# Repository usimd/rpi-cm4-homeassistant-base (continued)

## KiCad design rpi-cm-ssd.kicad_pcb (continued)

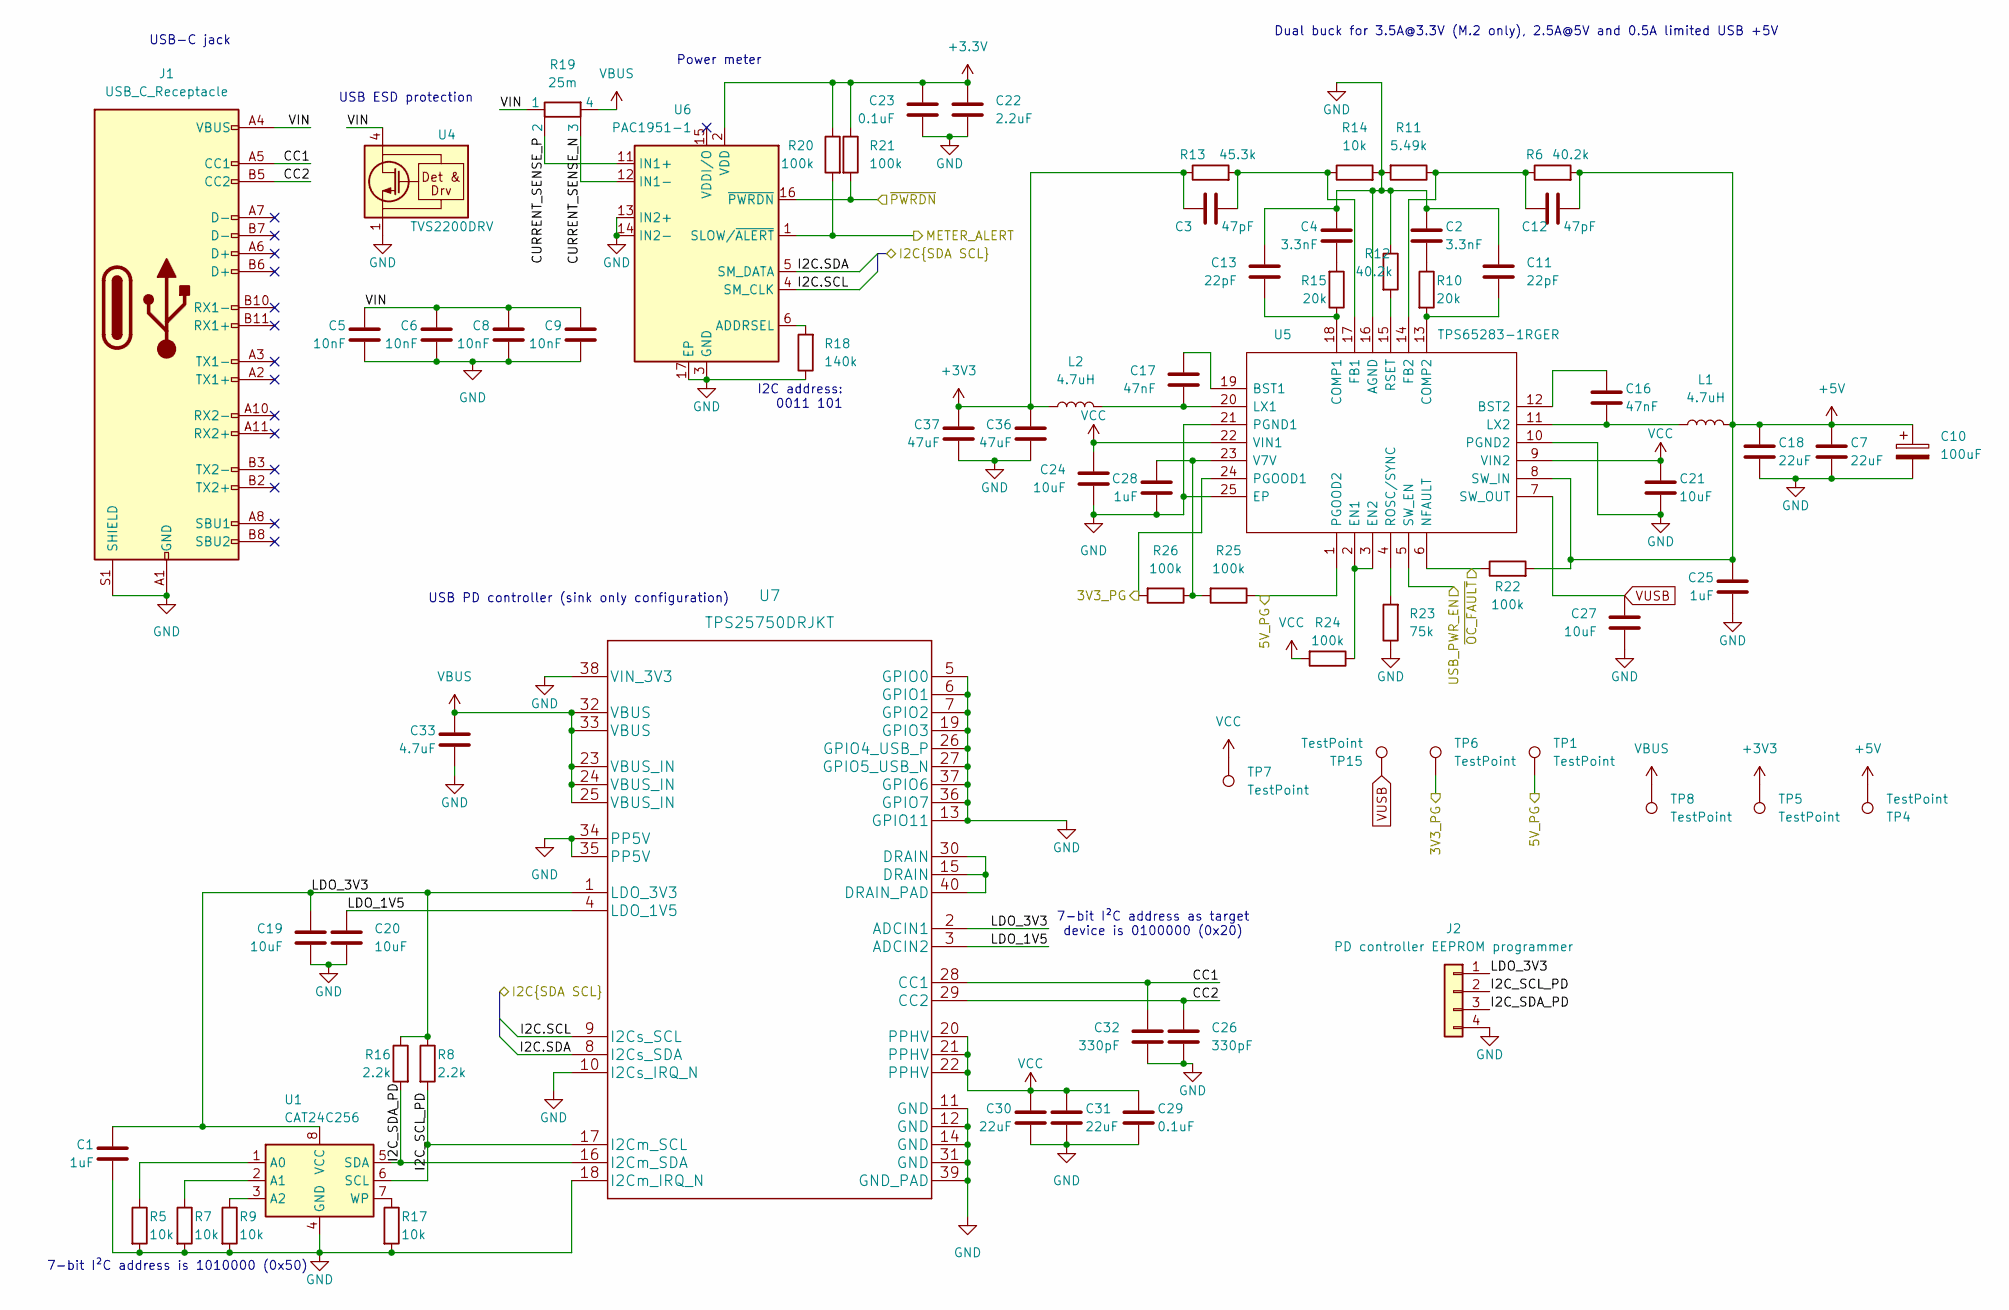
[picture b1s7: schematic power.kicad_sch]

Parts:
C1: 1uF; C_0402_1005Metric; MPN CL05B104KA5NNNC
C2, C4: 3.3nF; C_0402_1005Metric; MPN CC0402JRX7R9BB332
C3, C12: 47pF; C_0402_1005Metric; MPN C0402C470J5RACAUTO
C5, C6, C8, C9: 10nF; C_0402_1005Metric; MPN CC0402JRX7R9BB103
C7, C18: 22uF; C_0805_2012Metric; MPN CL21A226KOQNNNE
C10: 100uF; CP_EIA-3216-10_Kemet-I
C11, C13: 22pF; C_0402_1005Metric; MPN C0402C220K5RACTU
C16, C17: 47nF; C_0402_1005Metric; MPN UMK105B7472KV-F
C19, C20, C21, C24, C27: 10uF; C_0603_1608Metric; MPN GRM188R61E106KA73D
C22: 2.2uF; C_0402_1005Metric; MPN LMK105BJ225KV-F
C23: 0.1uF; C_0402_1005Metric; MPN CL05B104KA5NNNC
C25, C28: 1uF; C_0402_1005Metric; MPN GRM155R61E105KA12J
C26, C32: 330pF; C_0402_1005Metric; MPN 885012205058
C29: 0.1uF; C_1206_3216Metric; MPN CL05B104KA5NNNC
C30, C31: 22uF; C_1206_3216Metric; MPN CL31A226KAHNNNE
C33: 4.7uF; C_0603_1608Metric; MPN GRM188R6YA475KE15D
C36, C37: 47uF; C_0805_2012Metric; MPN CL21A226KOQNNNE
J1: USB_C_Receptacle; USB_C_Receptacle_Amphenol_12401610E4-2A; MPN 12401610E4#2A; LCSC Part # C5119948
J2: PD controller EEPROM programmer; PinHeader_1x04_P2.54mm_Vertical_SMD_Pin1Left
L1, L2: 4.7uH; L_Coilcraft_XAL60xx_6.36x6.56mm; MPN XAL6060-472MEC; LCSC Part # C3040367
R5, R7, R9, R14, R17: 10k; R_0402_1005Metric; MPN AC0402FR-0710KL
R6: 40.2k; R_0402_1005Metric; MPN RC0402FR-0740K2L
R8, R16: 2.2k; R_0402_1005Metric; MPN RC0402FR-132K2L
R10, R15: 20k; R_0402_1005Metric; MPN RC0402FR-1320KL
R11: 5.49k; R_0402_1005Metric; MPN RC0402FR-075K49L
R12: 40.2k; R_0402_1005Metric; MPN RC0402FR-0716K9L
R13: 45.3k; R_0402_1005Metric; MPN AC0402FR-0745K3L
R18: 140k; R_0402_1005Metric; MPN RC0402FR-07470RL
R19: 25m; R_Shunt_Vishay_WSK2512_6332Metric_T1.19mm; MPN WSK2512R0250DEA
R20: 100k; R_0402_1005Metric
R21: 100k; R_0805_2012Metric
R22, R24, R25, R26: 100k; R_0402_1005Metric; MPN RC0402FR-07100KL
R23: 75k; R_0402_1005Metric; MPN RC0402FR-07100KL
TP1, TP5, TP6, TP15: TestPoint; TestPoint_Keystone_5000-5004_Miniature
TP4, TP7, TP8: TestPoint; TestPoint_Pad_D1.0mm
U1: CAT24C256; SOIC-8_3.9x4.9mm_P1.27mm; MPN CAT24C256WI-GT3; LCSC Part # C36533643
U4: TVS2200DRV; WSON-6-1EP_2x2mm_P0.65mm_EP1x1.6mm; MPN TVS2200DRVR; LCSC Part # C523793
U5: TPS65283-1RGER; QFN50P400X400X100-25N-D; Manufacturer_Part_Number TPS65283-1RGER; Mouser Part Number 595-TPS65283-1RGER
U6: PAC1951-1; VQFN-16-1EP_3x3mm_P0.5mm_EP1.1x1.1mm_ThermalVias; MPN PAC1951T-1E/4MX; LCSC Part # C5226663
U7: TPS25750DRJKT; PTPS25750DRJKT; MPN TPS25750DRJKT; LCSC Part # C2868209

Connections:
+3.3V: C22.2, C23.1, R20.1, R21.1, U6.2 (VDD); also elsewhere on the board
+3V3: C3.1, C36.2, C37.2, L2.1, R13.1, TP5.1; also elsewhere on the board
+5V: C7.2, C10.1, C12.1, C18.2, C25.2, L1.2, R6.2, R22.2, TP4.1, U5.8 (SW_IN); also elsewhere on the board
/CM4 GPIO/3V3_PG: R26.2, TP6.1, U5.24 (PGOOD1); also elsewhere on the board
/CM4 GPIO/5V_PG: R25.1, TP1.1, U5.1 (PGOOD2); also elsewhere on the board
/CM4 GPIO/I2C.SCL: U6.4 (SM_CLK), U7.9 (I2Cs_SCL); also elsewhere on the board
/CM4 GPIO/I2C.SDA: U6.5 (SM_DATA), U7.8 (I2Cs_SDA); also elsewhere on the board
/Power/CC1: C32.2, J1.A5 (CC1), U7.28 (CC1)
/Power/CC2: C26.1, J1.B5 (CC2), U7.29 (CC2)
/Power/CURRENT_SENSE_N: R19.3, U6.12 (IN1-)
/Power/CURRENT_SENSE_P: R19.2, U6.11 (IN1+)
/Power/I2C_SCL_PD: J2.2, R8.2, U1.6 (SCL), U7.17 (I2Cm_SCL)
/Power/I2C_SDA_PD: J2.3, R16.2, U1.5 (SDA), U7.16 (I2Cm_SDA)
/Power/LDO_1V5: C20.1, U7.3 (ADCIN2), U7.4 (LDO_1V5)
/Power/LDO_3V3: C1.2, C19.2, J2.1, R8.1, R16.1, U1.8 (VCC), U7.1 (LDO_3V3), U7.2 (ADCIN1)
/Power/METER_ALERT: R20.2, U6.1 (SLOW/~ALERT)
/Power/USB_PWR_EN: U5.5 (SW_EN); also elsewhere on the board
/Power/VIN: C5.1, C6.1, C8.1, C9.1, J1.A4 (VBUS), J1.A9 (VBUS), J1.B4 (VBUS), J1.B9 (VBUS), R19.1, U4.4 (IN), U4.5 (IN), U4.6 (IN)
/Power/~OC_FAULT: R22.1, U5.6 (NFAULT); also elsewhere on the board
/Power/~PWRDN: R21.2, U6.16 (~PWRDN)
GND: C1.1, C2.1, C4.2, C5.2, C6.2, C7.1, C8.2, C9.2, C10.2, C11.2, C13.2, C18.1, C19.1, C20.2, C21.1, C22.1, C23.2, C24.1, C25.1, C26.2, C27.1, C28.1, C29.1, C30.1, C31.1, C32.1, C33.1, C36.1, C37.1, J1.A1 (GND), J1.A12 (GND), J1.B1 (GND), J1.B12 (GND), J1.S1 (SHIELD), J2.4, R5.2, R7.2, R9.2, R11.2, R12.1, R14.2, R17.2, R18.1, R23.1, U1.4 (GND), U4.1 (GND), U4.2 (GND), U4.3 (GND), U4.7 (GND), U5.10 (PGND2), U5.16 (AGND), U5.21 (PGND1), U5.25 (EP), U6.3 (GND), U6.7 (GND), U6.8 (GND), U6.9 (GND), U6.10 (GND), U6.13 (IN2+), U6.14 (IN2-), U6.17 (EP), U7.5 (GPIO0), U7.6 (GPIO1), U7.7 (GPIO2), U7.10 (I2Cs_IRQ_N), U7.11 (GND), U7.12 (GND), U7.13 (GPIO11), U7.14 (GND), U7.18 (I2Cm_IRQ_N), U7.19 (GPIO3), U7.26 (GPIO4_USB_P), U7.27 (GPIO5_USB_N), U7.31 (GND), U7.34 (PP5V), U7.35 (PP5V), U7.36 (GPIO7), U7.37 (GPIO6), U7.38 (VIN_3V3), U7.39 (GND_PAD); also elsewhere on the board
unnamed: C2.2, R10.1
unnamed: C4.1, R15.2
unnamed: R5.1, U1.1 (A0)
unnamed: R7.1, U1.2 (A1)
unnamed: R9.1, U1.3 (A2)
unnamed: R17.1, U1.7 (WP)
unnamed: C17.2, U5.19 (BST1)
unnamed: C16.2, U5.12 (BST2)
unnamed: C13.1, R15.1, U5.18 (COMP1)
unnamed: C11.1, R10.2, U5.13 (COMP2)
unnamed: R24.1, U5.2 (EN1), U5.3 (EN2)
unnamed: C3.2, R13.2, R14.1, U5.17 (FB1)
unnamed: C12.2, R6.1, R11.1, U5.14 (FB2)
unnamed: C17.1, L2.2, U5.20 (LX1)
unnamed: C16.1, L1.1, U5.11 (LX2)
unnamed: R23.2, U5.4 (ROSC/SYNC)
unnamed: R12.2, U5.15 (RSET)
unnamed: C28.2, R25.2, R26.1, U5.23 (V7V)
unnamed: R18.2, U6.6 (ADDRSEL)
unnamed: U7.15 (DRAIN), U7.30 (DRAIN), U7.40 (DRAIN_PAD)
VBUS: C33.2, R19.4, TP8.1, U7.23 (VBUS_IN), U7.24 (VBUS_IN), U7.25 (VBUS_IN), U7.32 (VBUS), U7.33 (VBUS)
VCC: C21.2, C24.2, C29.2, C30.2, C31.2, R24.2, TP7.1, U5.9 (VIN2), U5.22 (VIN1), U7.20 (PPHV), U7.21 (PPHV), U7.22 (PPHV)
VUSB: C27.2, TP15.1, U5.7 (SW_OUT); also elsewhere on the board

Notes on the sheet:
7-bit I²C address as target device is 0100000 (0x20)
USB ESD protection
Dual buck for 3.5A@3.3V (M.2 only), 2.5A@5V and 0.5A limited USB +5V
USB PD controller (sink only configuration)
7-bit I²C address is 1010000 (0x50)
Power meter
USB-C jack
I2C address: 0011 101

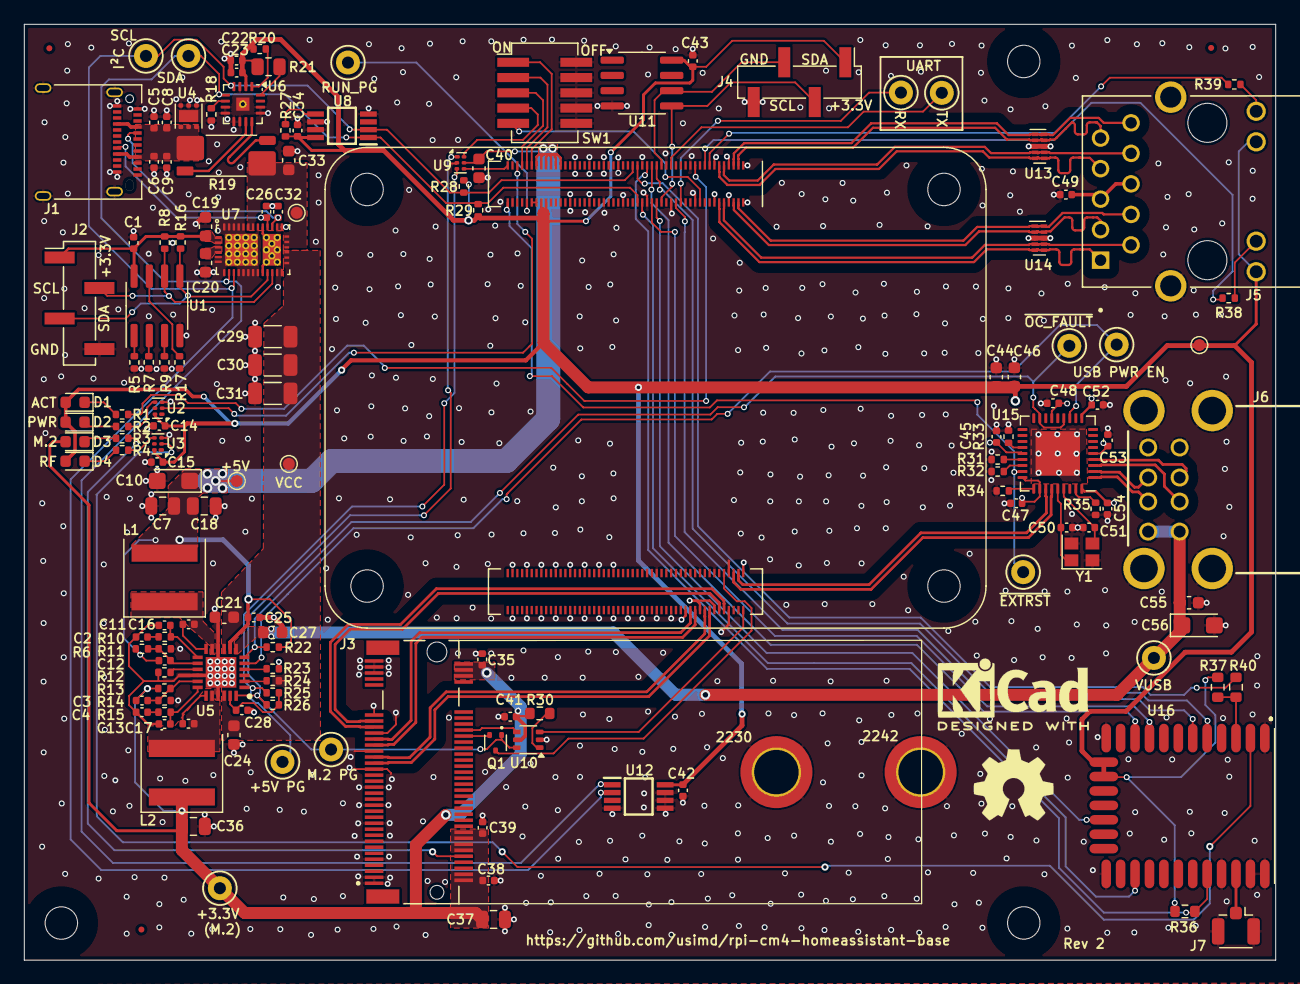
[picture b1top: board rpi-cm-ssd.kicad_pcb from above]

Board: 4 copper layers, 104.1 x 77.9 mm, 153 parts (0 on the bottom side), 115 nets.

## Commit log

2022-11-20 Initial import
2022-12-08 Add bus debug test points
    For easier debugging the I2C and SPI bus are being branched to via test
    pads. Some enhancements to the PD controller are made by connecting PP5V
    to ground. Also corrects the footprint of the energy meter.
2022-12-08 Update readme, add PD controller config
2025-01-28 Prep Rev2
2025-02-02 Rev 2
